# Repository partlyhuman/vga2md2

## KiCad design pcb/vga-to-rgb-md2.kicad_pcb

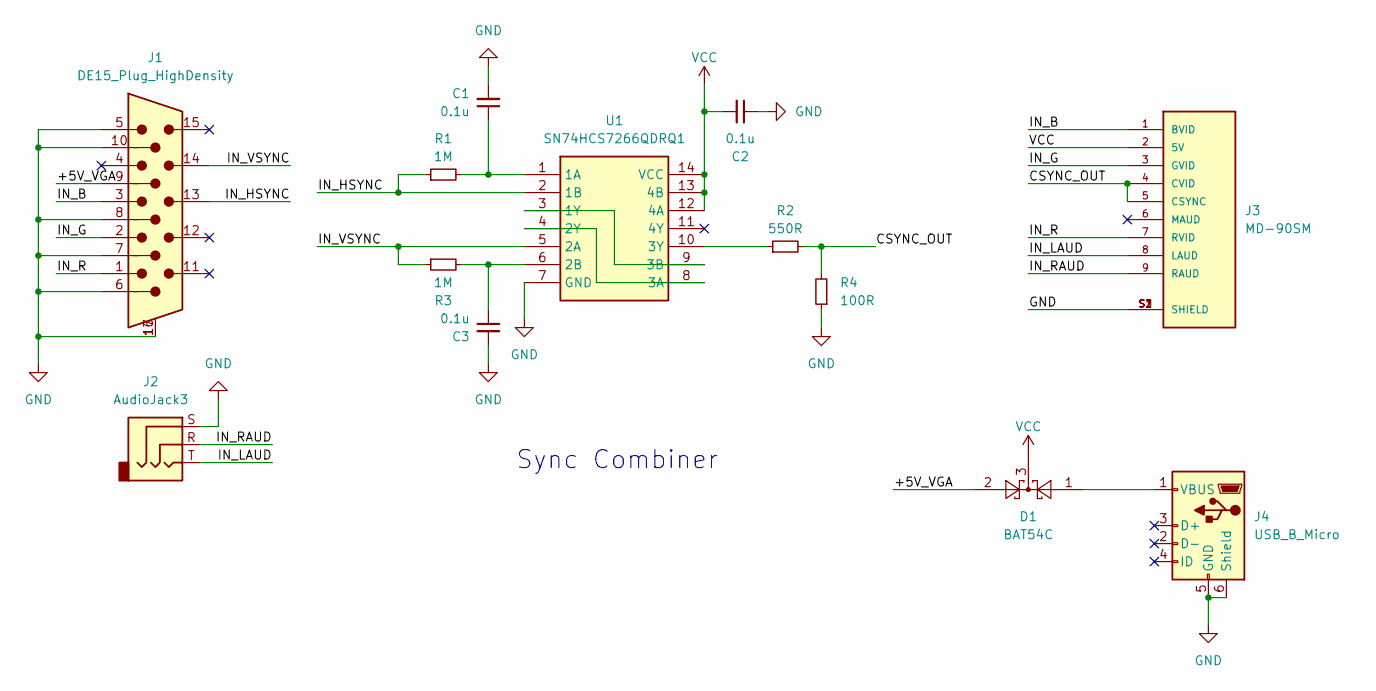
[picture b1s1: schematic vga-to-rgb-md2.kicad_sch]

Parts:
C1, C2, C3: 0.1u; C_0805_2012Metric_Pad1.18x1.45mm_HandSolder
D1: BAT54C; SOT-23
J1: DE15_Plug_HighDensity; DSUB-15-HD_Male_Horizontal_P2.29x2.54mm_EdgePinOffset9.40mm
J2: AudioJack3; Jack_3.5mm_CUI_SJ-3523-SMT_Horizontal
J3: MD-90SM; CUI_MD-90SM; PARTREV 02/18/2022
J4: USB_B_Micro; USB_Micro-B_Molex-105017-0001
R1, R3: 1M; R_0805_2012Metric_Pad1.20x1.40mm_HandSolder
R2: 550R; R_0805_2012Metric_Pad1.20x1.40mm_HandSolder
R4: 100R; R_0805_2012Metric_Pad1.20x1.40mm_HandSolder
U1: SN74HCS7266QDRQ1; SOIC-14_3.9x8.7mm_P1.27mm; Manufacturer_Part_Number SN74HCS7266PWR; Mouser Part Number 595-SN74HCS7266PWR

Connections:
/+5V_VGA: D1.2, J1.9
/CSYNC_OUT: J3.4 (CVID), J3.5 (CSYNC), R2.2, R4.2
/IN_B: J1.3, J3.1 (BVID)
/IN_G: J1.2, J3.3 (GVID)
/IN_HSYNC: J1.13, R1.1, U1.2 (1B)
/IN_LAUD: J2.T, J3.8 (LAUD)
/IN_R: J1.1, J3.7 (RVID)
/IN_RAUD: J2.R, J3.9 (RAUD)
/IN_VSYNC: J1.14, R3.1, U1.5 (2A)
GND: C1.2, C2.1, C3.2, J1.5, J1.6, J1.7, J1.8, J1.10, J1.16 (Mount), J1.17 (Mount), J2.S, J3.S1 (SHIELD), J3.S2 (SHIELD), J3.S3 (SHIELD), J4.5 (GND), J4.6 (Shield), R4.1, U1.7 (GND)
unnamed: D1.1, J4.1 (VBUS)
unnamed: C1.1, R1.2, U1.1 (1A)
unnamed: U1.3 (1Y), U1.9 (3B)
unnamed: C3.1, R3.2, U1.6 (2B)
unnamed: U1.4 (2Y), U1.8 (3A)
unnamed: R2.1, U1.10 (3Y)
VCC: C2.2, D1.3, J3.2 (5V), U1.12 (4A), U1.13 (4B), U1.14 (VCC)

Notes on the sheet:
Sync Combiner

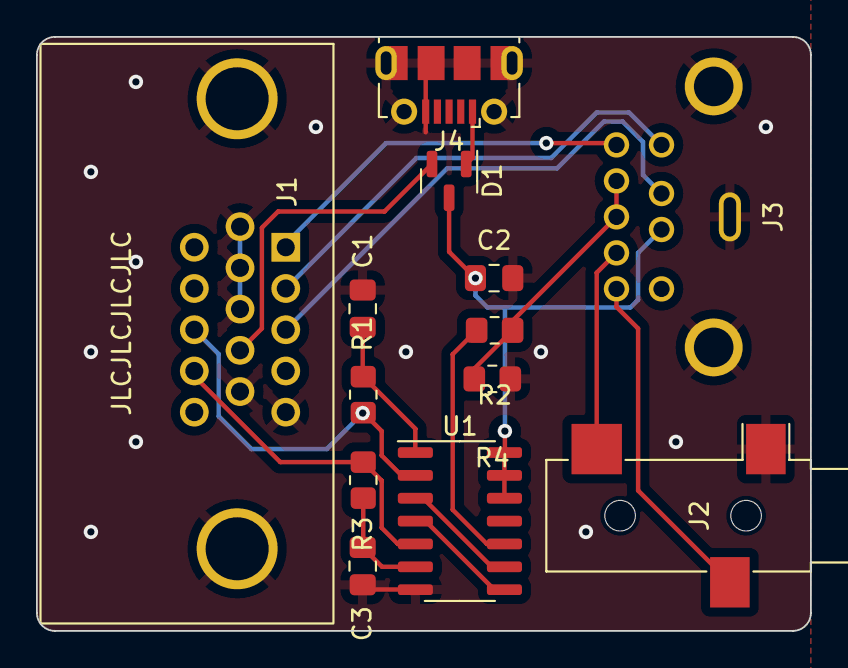
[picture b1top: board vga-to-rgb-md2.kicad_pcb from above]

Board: 2 copper layers, 43.0 x 33.0 mm, 13 parts (0 on the bottom side), 17 nets.

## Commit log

2023-12-19 Sketch
2023-12-22 Adds external 5V
2024-02-09 Move stereo jack to face outside so VGA can sit flush against PCs
